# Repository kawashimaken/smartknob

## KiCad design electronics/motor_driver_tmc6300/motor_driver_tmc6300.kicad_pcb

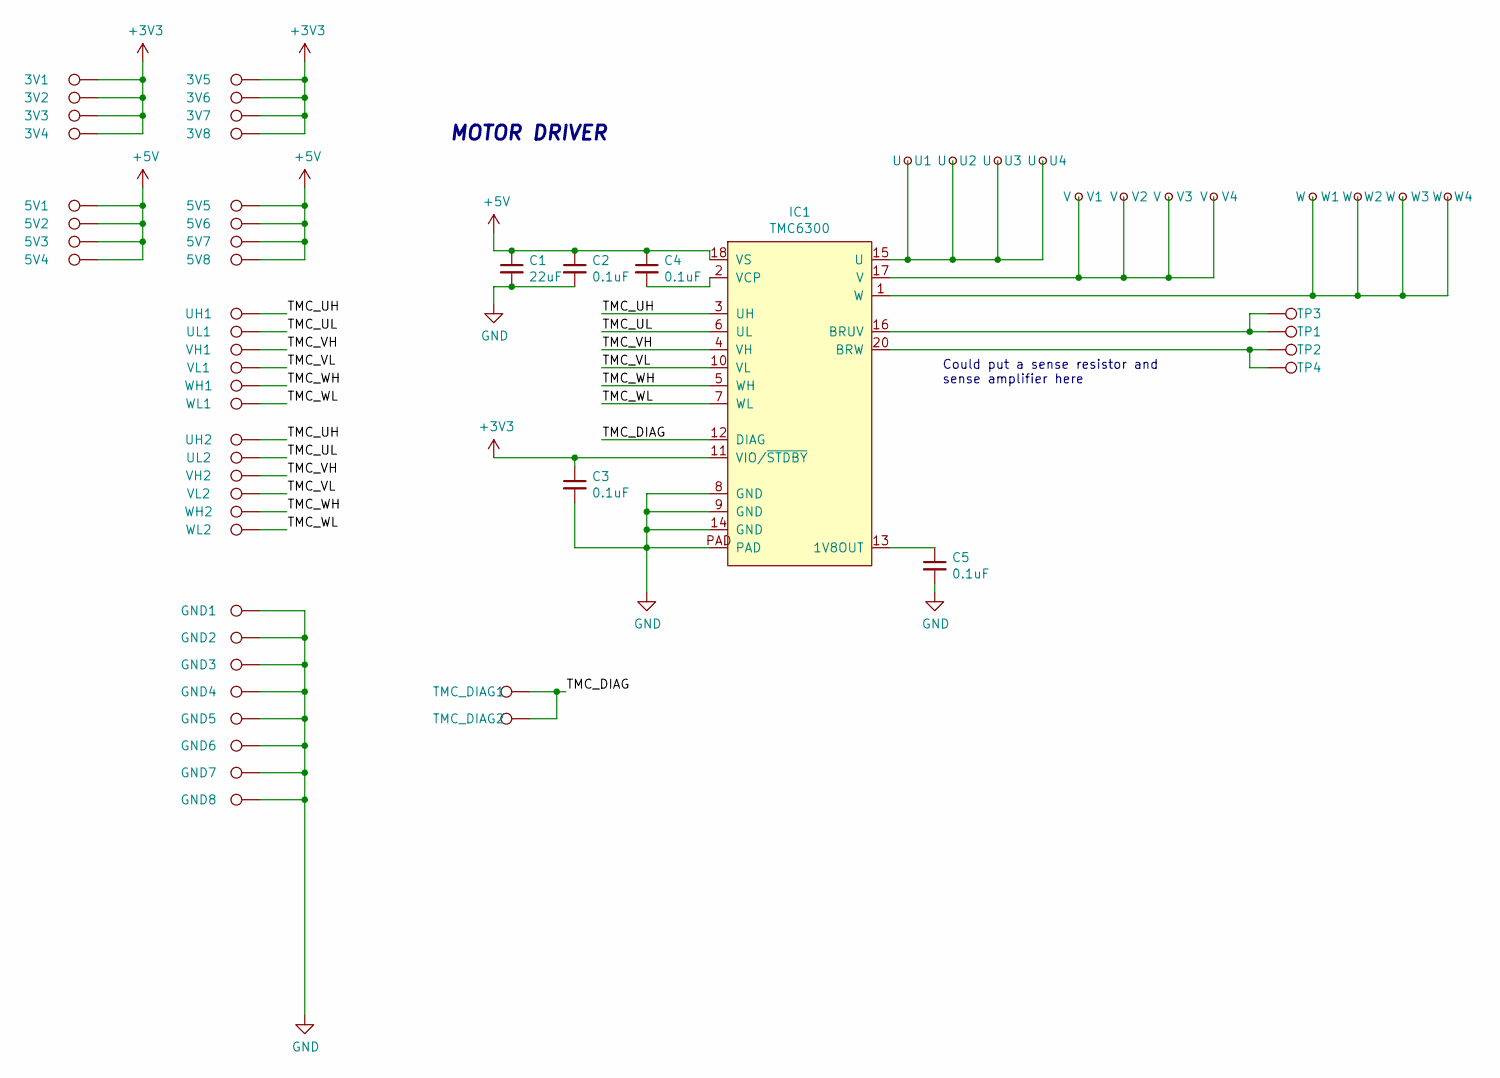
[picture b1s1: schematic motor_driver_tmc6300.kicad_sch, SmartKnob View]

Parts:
3V1, 3V2, 3V3, 3V4, 3V5, 3V6, 3V7, 3V8, 5V1, 5V2, 5V3, 5V4, 5V5, 5V6, 5V7, 5V8: TestPoint; kawashima_TestPoint_THTPad_D1.5mm_Drill0.7mm
C1: 22uF; C_0805_2012Metric_Pad1.18x1.45mm_HandSolder; LCSC C98190
C2, C3, C4, C5: 0.1uF; C_0603_1608Metric_Pad1.08x0.95mm_HandSolder; LCSC C1591
GND1, GND2, GND3, GND4, GND5, GND6, GND7, GND8: TestPoint; kawashima_TestPoint_THTPad_D1.5mm_Drill0.7mm
IC1: TMC6300; QFN-20-1EP_3x3mm_P0.4mm_EP1.65x1.65mm_ThermalVias_LargerVia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; Digikey TMC6300-LA-T
TMC_DIAG1, TMC_DIAG2: TestPoint; kawashima_TestPoint_THTPad_D1.5mm_Drill0.7mm
TP1, TP2, TP3, TP4: TestPoint; kawashima_TestPoint_THTPad_D1.5mm_Drill0.7mm
U1, U2, U3, U4: U; kawashima_TestPoint_THTPad_D1.5mm_Drill0.7mm
UH1, UH2: TestPoint; kawashima_TestPoint_THTPad_D1.5mm_Drill0.7mm
UL1, UL2: TestPoint; kawashima_TestPoint_THTPad_D1.5mm_Drill0.7mm
V1, V2, V3, V4: V; kawashima_TestPoint_THTPad_D1.5mm_Drill0.7mm
VH1, VH2: TestPoint; kawashima_TestPoint_THTPad_D1.5mm_Drill0.7mm
VL1, VL2: TestPoint; kawashima_TestPoint_THTPad_D1.5mm_Drill0.7mm
W1, W2, W3, W4: W; kawashima_TestPoint_THTPad_D1.5mm_Drill0.7mm
WH1, WH2: TestPoint; kawashima_TestPoint_THTPad_D1.5mm_Drill0.7mm
WL1, WL2: TestPoint; kawashima_TestPoint_THTPad_D1.5mm_Drill0.7mm

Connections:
+3V3: 3V1.1, 3V2.1, 3V3.1, 3V4.1, 3V5.1, 3V6.1, 3V7.1, 3V8.1, C3.1, IC1.11 (VIO/~STDBY)
+5V: 5V1.1, 5V2.1, 5V3.1, 5V4.1, 5V5.1, 5V6.1, 5V7.1, 5V8.1, C1.1, C2.1, C4.1, IC1.18 (VS)
/TMC_DIAG: IC1.12 (DIAG), TMC_DIAG1.1, TMC_DIAG2.1
/TMC_UH: IC1.3 (UH), UH1.1, UH2.1
/TMC_UL: IC1.6 (UL), UL1.1, UL2.1
/TMC_VH: IC1.4 (VH), VH1.1, VH2.1
/TMC_VL: IC1.10 (VL), VL1.1, VL2.1
/TMC_WH: IC1.5 (WH), WH1.1, WH2.1
/TMC_WL: IC1.7 (WL), WL1.1, WL2.1
GND: C1.2, C2.2, C3.2, C5.2, GND1.1, GND2.1, GND3.1, GND4.1, GND5.1, GND6.1, GND7.1, GND8.1, IC1.8 (GND), IC1.9 (GND), IC1.14 (GND), IC1.PAD
unnamed: C5.1, IC1.13 (1V8OUT)
unnamed: IC1.16 (BRUV), TP1.1, TP3.1
unnamed: IC1.20 (BRW), TP2.1, TP4.1
unnamed: IC1.15 (U), U1.1, U2.1, U3.1, U4.1
unnamed: IC1.17 (V), V1.1, V2.1, V3.1, V4.1
unnamed: C4.2, IC1.2 (VCP)
unnamed: IC1.1 (W), W1.1, W2.1, W3.1, W4.1

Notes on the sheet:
Could put a sense resistor and sense amplifier here
MOTOR DRIVER

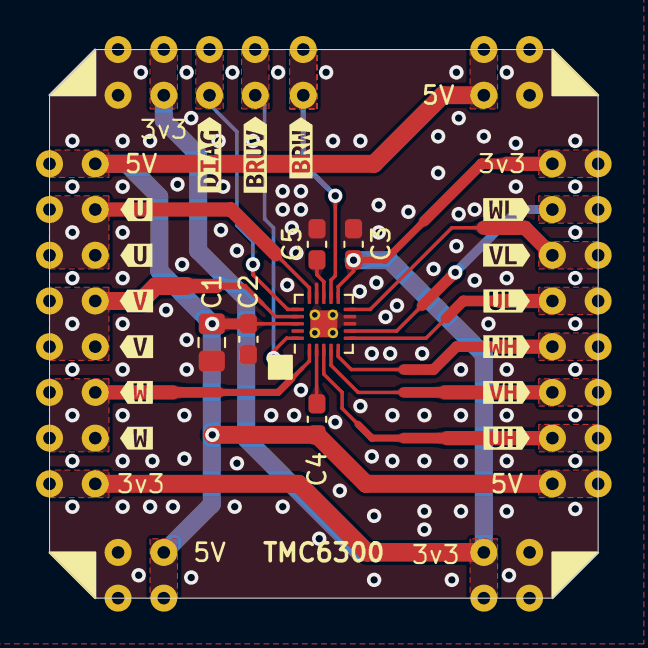
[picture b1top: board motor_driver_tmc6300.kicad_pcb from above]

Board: 2 copper layers, 30.5 x 30.5 mm, 75 parts (0 on the bottom side), 17 nets.

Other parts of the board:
kibuzzard-6701E86E, kibuzzard-6701E86E#2: G***; kibuzzard-6701E86E
kibuzzard-6701E87B, kibuzzard-6701E87B#2: G***; kibuzzard-6701E87B
kibuzzard-6701E882, kibuzzard-6701E882#2: G***; kibuzzard-6701E882
kibuzzard-670234D9: G***; kibuzzard-670234D9
kibuzzard-6702202C: G***; kibuzzard-6702202C
kibuzzard-6702204D: G***; kibuzzard-6702204D
kibuzzard-6702206A: G***; kibuzzard-6702206A
kibuzzard-67022038: G***; kibuzzard-67022038
kibuzzard-67022043: G***; kibuzzard-67022043
kibuzzard-67022085: G***; kibuzzard-67022085
kibuzzard-67032619: G***; kibuzzard-67032619
kibuzzard-67032626: G***; kibuzzard-67032626

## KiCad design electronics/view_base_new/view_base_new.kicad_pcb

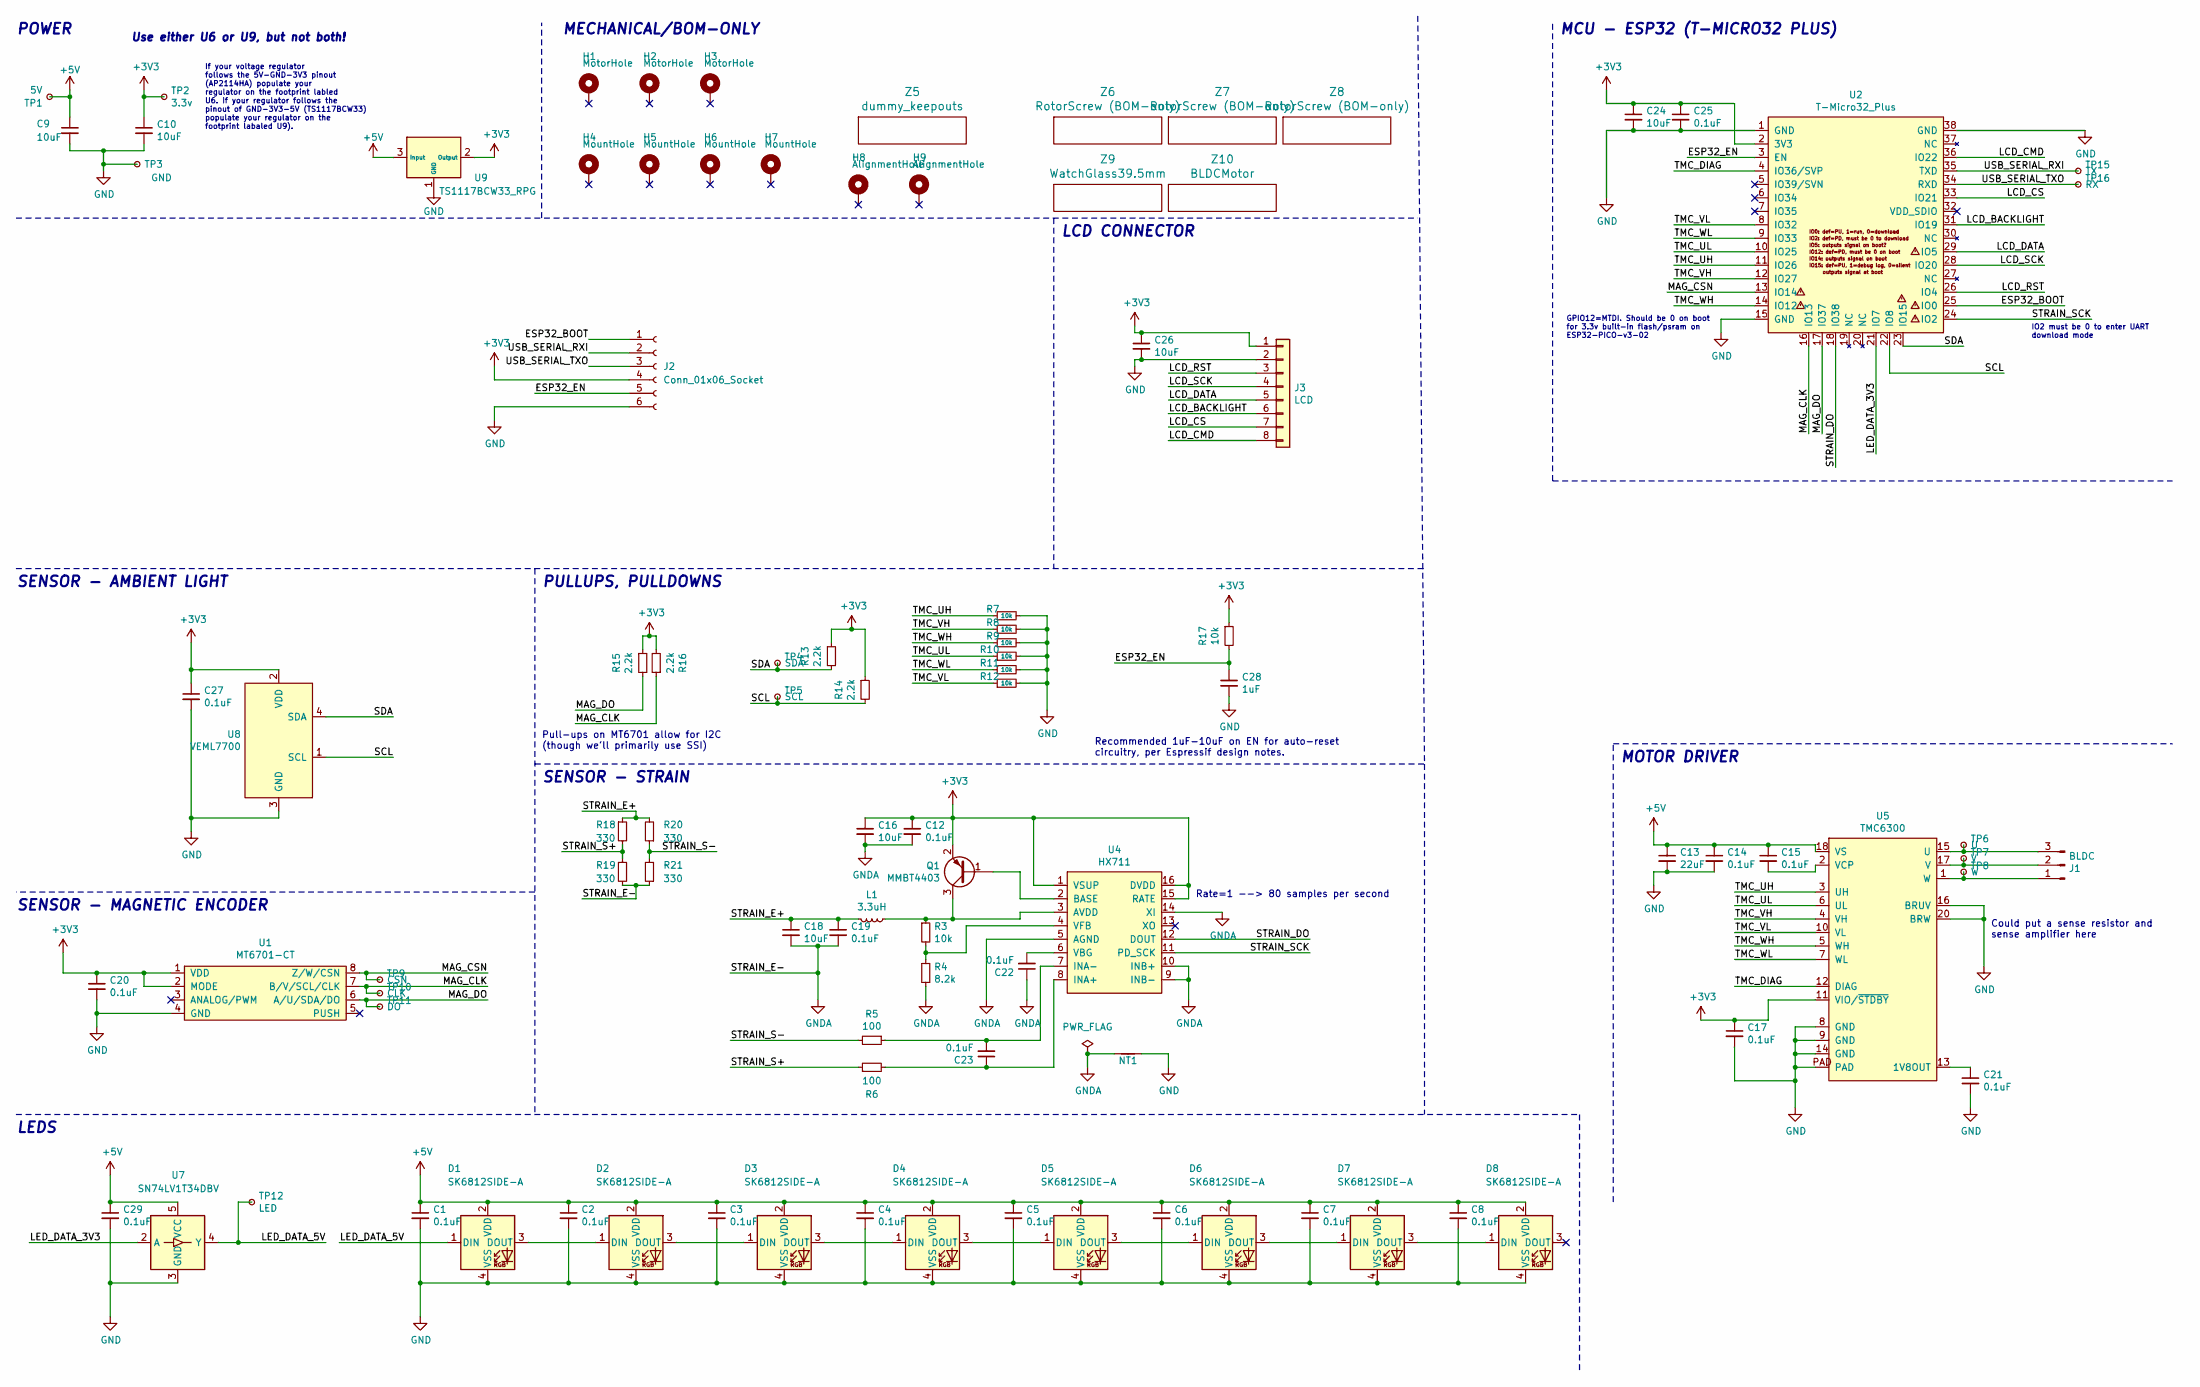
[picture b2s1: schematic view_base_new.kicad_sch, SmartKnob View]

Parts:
C1, C2, C3, C4, C5, C6, C7, C8, C12, C14, C15, C17, C19, C20, C21, C22, C23: 0.1uF; C_0603_1608Metric; LCSC C1591
C9, C10, C16, C18, C24: 10uF; C_0805_2012Metric; LCSC C15850
C13: 22uF; C_0805_2012Metric; LCSC C98190
C25, C27, C29: 0.1uF; C_0603_1608Metric_Pad1.08x0.95mm_HandSolder; LCSC C1591
C26: 10uF; C_0805_2012Metric_Pad1.18x1.45mm_HandSolder; LCSC C15850
C28: 1uF; C_0603_1608Metric_Pad1.08x0.95mm_HandSolder; Mouser 187-CL10A105KA8NNNC
D1, D2, D3, D4, D5, D6, D7, D8: SK6812SIDE-A; SK6812-SIDE-A; Digikey 1528-4691-ND
H1, H2, H3: MotorHole; MountingHole_M1.6; LCSC C2931389
H4, H5, H6, H7: MountHole; MountingHole_2.2mm_M2_ISO7380_Pad_NonVirtual; LCSC C2911210 or C2911532 (screw), C2961595 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
H8, H9: AlignmentHole; MountingHole_2.2mm_M2_ISO7380_Pad_NonVirtual
J1: BLDC; 532610371; LCSC C293630
J2: Conn_01x06_Socket; PinHeader_1x06_P2.54mm_Vertical
J3: LCD; SolderPads_2mm_8
L1: 3.3uH; L_0805_2012Metric; LCSC C307744
NT1: NetTie_2; NetTie-2_SMD_Pad0.5mm
Q1: MMBT4403; SOT-23; LCSC C78864
R3, R7, R8, R9, R10, R11, R12, R17: 10k; R_0603_1608Metric; LCSC C98220
R4: 8.2k; R_0603_1608Metric; LCSC C114637
R5, R6: 100; R_0603_1608Metric; LCSC C319953
R13, R14, R15, R16: 2.2k; R_0603_1608Metric; LCSC C4190
R18, R19, R20, R21: 330; R_2512_6332Metric; LCSC C19866
TP1: 5V; TestPoint_Pad_D2.0mm_ValueSilk
TP2: 3.3v; TestPoint_Pad_D2.0mm_ValueSilk
TP3: GND; TestPoint_Pad_D2.0mm_ValueSilk
TP4: SDA; TestPoint_Pad_D2.0mm_ValueSilk
TP5: SCL; TestPoint_Pad_D2.0mm_ValueSilk
TP6: U; TestPoint_Pad_D2.0mm_ValueSilk
TP7: V; TestPoint_Pad_D2.0mm_ValueSilk
TP8: W; TestPoint_Pad_D2.0mm_ValueSilk
TP9: CSN; TestPoint_Pad_D2.0mm_ValueSilk
TP10: CLK; TestPoint_Pad_D2.0mm_ValueSilk
TP11: DO; TestPoint_Pad_D2.0mm_ValueSilk
TP12: LED; TestPoint_Pad_D2.0mm_ValueSilk
TP15: TX; TestPoint_Pad_D2.0mm_ValueSilk
TP16: RX; TestPoint_Pad_D2.0mm_ValueSilk
U1: MT6701-CT; SOIC-8_3.9x4.9mm_P1.27mm; LCSC C2856764, or C3003196
U2: T-Micro32_Plus; T-Micro32; Digikey N/A
U4: HX711; SOIC-16_3.9x9.9mm_P1.27mm; LCSC C43656
U5: TMC6300; QFN-20-1EP_3x3mm_P0.4mm_EP1.65x1.65mm_ThermalVias_LargerVia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; Digikey TMC6300-LA-T
U7: SN74LV1T34DBV; SOT-23-5; LCSC C100024
U8: VEML7700; VEML7700-TOP; Digikey VEML7700-TT
U9: TS1117BCW33_RPG; SOT-223-3_TabPin2_GndOutIn; LCSC C6186, C35879, or others
Z5: dummy_keepouts; ViewKeepouts3d
Z6, Z7, Z8: RotorScrew (BOM-only); bom_only_no_pin
Z9: WatchGlass39.5mm; bom_only_no_pin
Z10: BLDCMotor; bom_only_no_pin

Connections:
+3V3: C10.1, C12.1, C16.1, C17.1, C20.1, C24.1, C25.1, C26.1, C27.1, J2.4, J3.1, Q1.2 (E), R13.1, R14.1, R15.1, R16.2, R17.1, TP2.1, U1.1 (VDD), U1.2 (MODE), U2.2 (3V3), U4.1 (VSUP), U4.15 (RATE), U4.16 (DVDD), U5.11 (VIO/~STDBY), U8.2 (VDD), U9.2 (Output)
+5V: C1.1, C2.1, C3.1, C4.1, C5.1, C6.1, C7.1, C8.1, C9.1, C13.1, C14.1, C15.1, C29.1, D1.2 (VDD), D2.2 (VDD), D3.2 (VDD), D4.2 (VDD), D5.2 (VDD), D6.2 (VDD), D7.2 (VDD), D8.2 (VDD), TP1.1, U5.18 (VS), U7.5 (VCC), U9.3 (Input)
/ESP32_BOOT: J2.1, U2.25 (IO0)
/ESP32_EN: C28.1, J2.5, R17.2, U2.3 (EN)
/LCD_BACKLIGHT: J3.6, U2.31 (IO19)
/LCD_CMD: J3.8, U2.36 (IO22)
/LCD_CS: J3.7, U2.33 (IO21)
/LCD_DATA: J3.5, U2.29 (IO5)
/LCD_RST: J3.3, U2.26 (IO4)
/LCD_SCK: J3.4, U2.28 (IO20)
/LED_DATA_3V3: U2.21 (IO7), U7.2 (A)
/LED_DATA_5V: D1.1 (DIN), TP12.1, U7.4 (Y)
/MAG_CLK: R16.1, TP10.1, U1.7 (B/V/SCL/CLK), U2.16 (IO13)
/MAG_CSN: TP9.1, U1.8 (Z/W/CSN), U2.13 (IO14)
/MAG_DO: R15.2, TP11.1, U1.6 (A/U/SDA/DO), U2.17 (IO37)
/SCL: R14.2, TP5.1, U2.22 (IO8), U8.1 (SCL)
/SDA: R13.2, TP4.1, U2.23 (IO15), U8.4 (SDA)
/STRAIN_DO: U2.18 (IO38), U4.12 (DOUT)
/STRAIN_E+: C18.1, C19.1, L1.2, R18.1, R20.2
/STRAIN_S+: R6.1, R18.2, R19.1
/STRAIN_S-: R5.2, R20.1, R21.2
/STRAIN_SCK: U2.24 (IO2), U4.11 (PD_SCK)
/TMC_DIAG: U2.4 (IO36/SVP), U5.12 (DIAG)
/TMC_UH: R7.1, U2.11 (IO26), U5.3 (UH)
/TMC_UL: R10.1, U2.10 (IO25), U5.6 (UL)
/TMC_VH: R8.1, U2.12 (IO27), U5.4 (VH)
/TMC_VL: R12.1, U2.8 (IO32), U5.10 (VL)
/TMC_WH: R9.1, U2.14 (IO12), U5.5 (WH)
/TMC_WL: R11.1, U2.9 (IO33), U5.7 (WL)
/USB_SERIAL_RXI: J2.2, TP15.1, U2.35 (TXD)
/USB_SERIAL_TXO: J2.3, TP16.1, U2.34 (RXD)
GND: C1.2, C2.2, C3.2, C4.2, C5.2, C6.2, C7.2, C8.2, C9.2, C10.2, C13.2, C14.2, C17.2, C20.2, C21.2, C24.2, C25.2, C26.2, C27.2, C28.2, C29.2, D1.4 (VSS), D2.4 (VSS), D3.4 (VSS), D4.4 (VSS), D5.4 (VSS), D6.4 (VSS), D7.4 (VSS), D8.4 (VSS), J2.6, J3.2, NT1.2, R7.2, R8.2, R9.2, R10.2, R11.2, R12.2, TP3.1, U1.4 (GND), U2.1 (GND), U2.15 (GND), U2.38 (GND), U5.8 (GND), U5.9 (GND), U5.14 (GND), U5.16 (BRUV), U5.20 (BRW), U5.PAD, U7.3 (GND), U8.3 (GND), U9.1 (GND)
GNDA: C12.2, C16.2, C18.2, C19.2, C22.1, NT1.1, R4.2, R19.2, R21.1, U4.5 (AGND), U4.9 (INB-), U4.10 (INB+), U4.14 (XI)
unnamed: D1.3 (DOUT), D2.1 (DIN)
unnamed: D2.3 (DOUT), D3.1 (DIN)
unnamed: D3.3 (DOUT), D4.1 (DIN)
unnamed: D4.3 (DOUT), D5.1 (DIN)
unnamed: D5.3 (DOUT), D6.1 (DIN)
unnamed: D6.3 (DOUT), D7.1 (DIN)
unnamed: D7.3 (DOUT), D8.1 (DIN)
unnamed: J1.1, TP8.1, U5.1 (W)
unnamed: J1.2, TP7.1, U5.17 (V)
unnamed: J1.3, TP6.1, U5.15 (U)
unnamed: Q1.1 (B), U4.2 (BASE)
unnamed: L1.1, Q1.3 (C), R3.1, U4.3 (AVDD)
unnamed: C23.1, R6.2, U4.8 (INA+)
unnamed: C23.2, R5.1, U4.7 (INA-)
unnamed: C22.2, U4.6 (VBG)
unnamed: R3.2, R4.1, U4.4 (VFB)
unnamed: C21.1, U5.13 (1V8OUT)
unnamed: C15.2, U5.2 (VCP)

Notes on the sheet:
POWER
Could put a sense resistor and sense amplifier here
MCU - ESP32 (T-MICRO32 PLUS)
If your voltage regulator follows the 5V-GND-3V3 pinout (AP2114HA) populate your regulator on the footprint labled U6. If your regulator follows the pinout of GND-3V3-5V (TS1117BCW33) populate your regulator on the footprint labaled U9).
SENSOR - MAGNETIC ENCODER
MOTOR DRIVER
MECHANICAL/BOM-ONLY
IO2 must be 0 to enter UART download mode
GPIO12=MTDI. Should be 0 on boot for 3.3v built-in flash/psram on ESP32-PICO-v3-02
Pull-ups on MT6701 allow for I2C (though we'll primarily use SSI)
Use either U6 or U9, but not both!
Rate=1 --> 80 samples per second
SENSOR - AMBIENT LIGHT
Recommended 1uF-10uF on EN for auto-reset circuitry, per Espressif design notes.
SENSOR - STRAIN
LEDS
PULLUPS, PULLDOWNS
LCD CONNECTOR

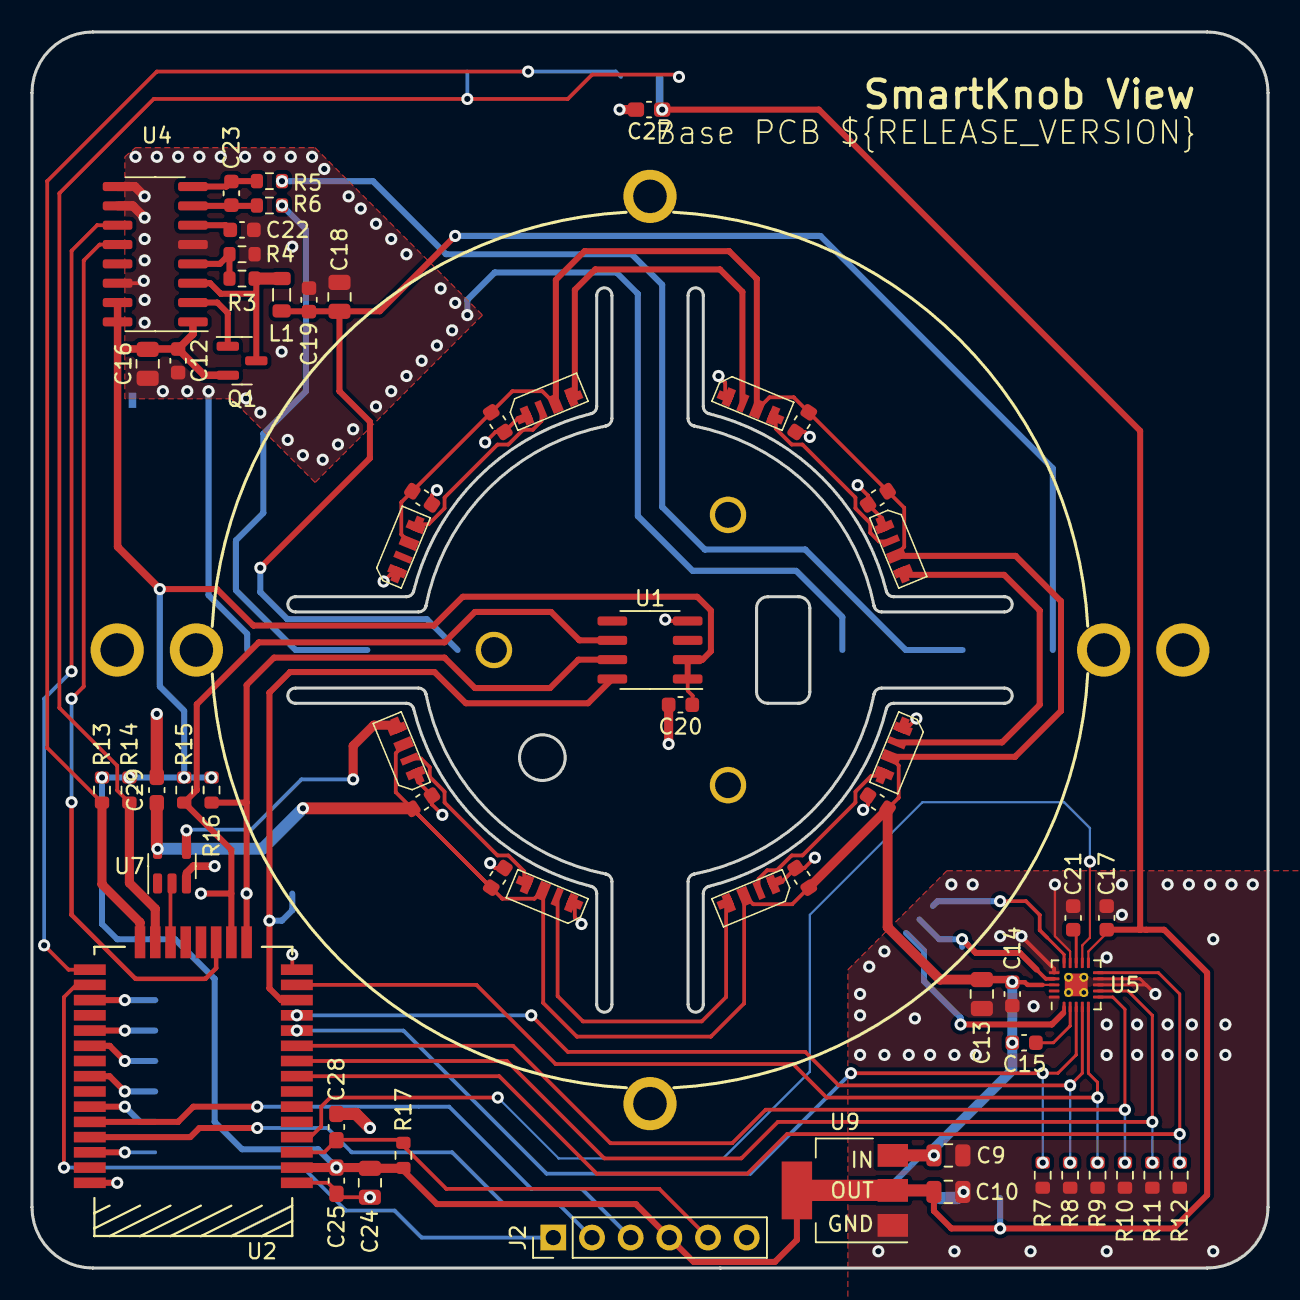
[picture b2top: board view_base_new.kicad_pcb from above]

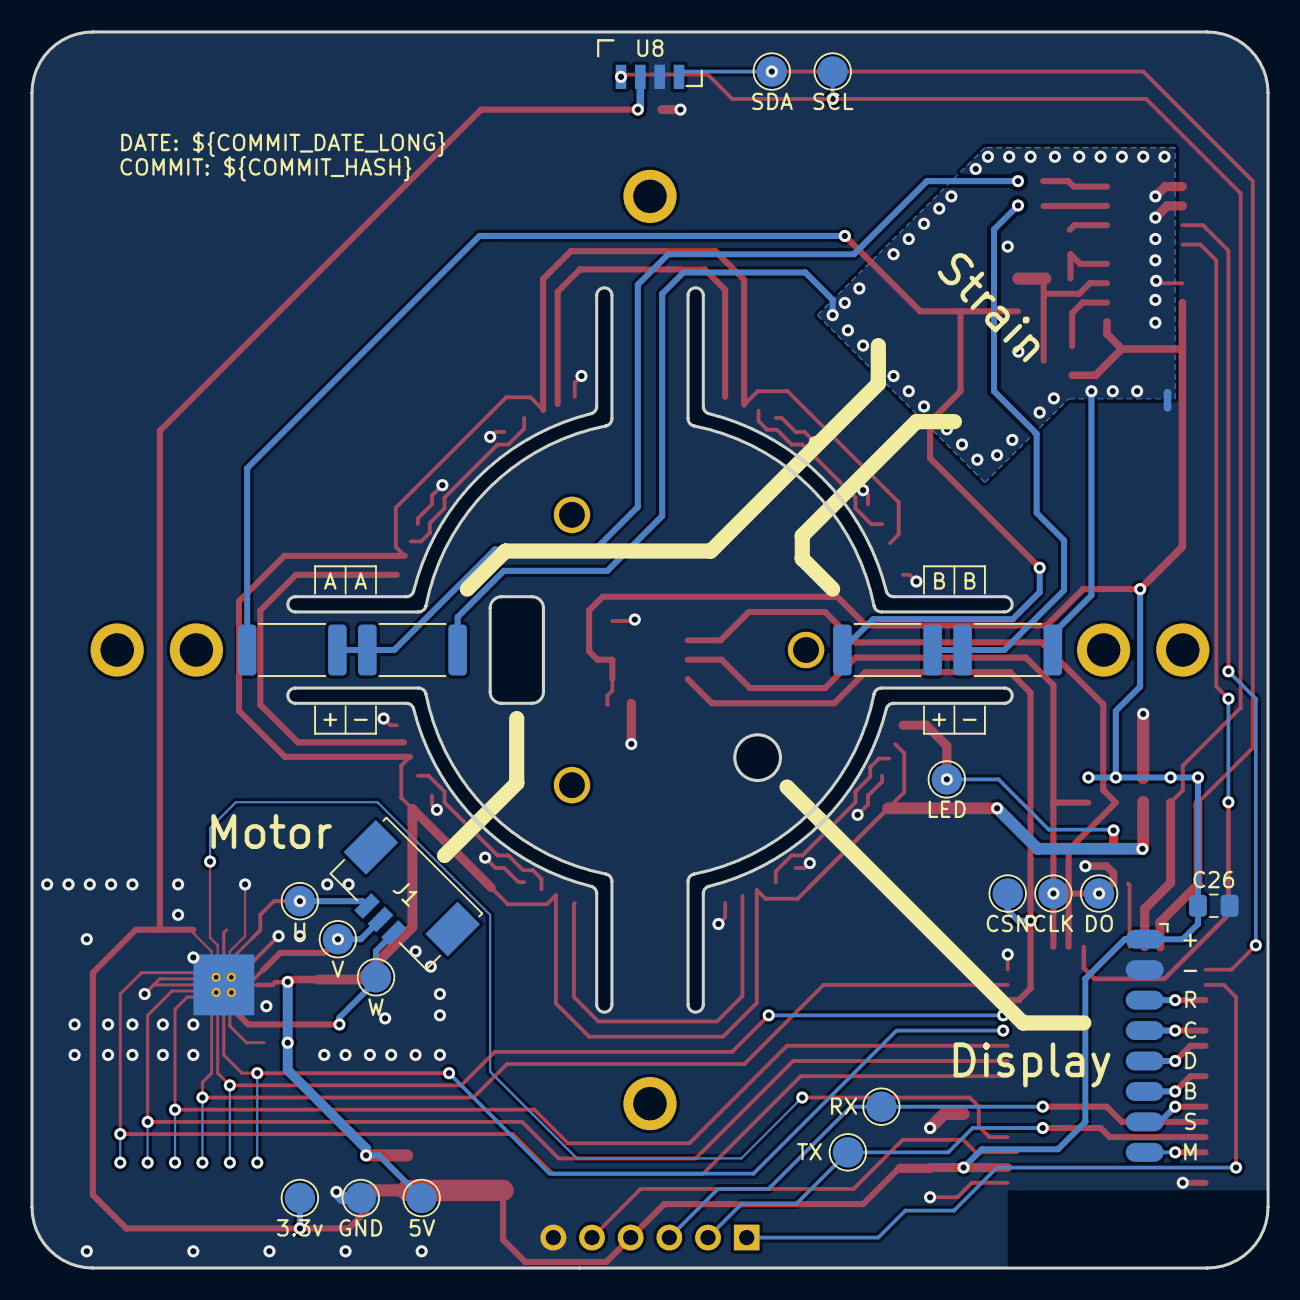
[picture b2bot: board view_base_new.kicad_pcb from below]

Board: 2 copper layers, 81.2 x 81.2 mm, 97 parts (23 on the bottom side), 51 nets.

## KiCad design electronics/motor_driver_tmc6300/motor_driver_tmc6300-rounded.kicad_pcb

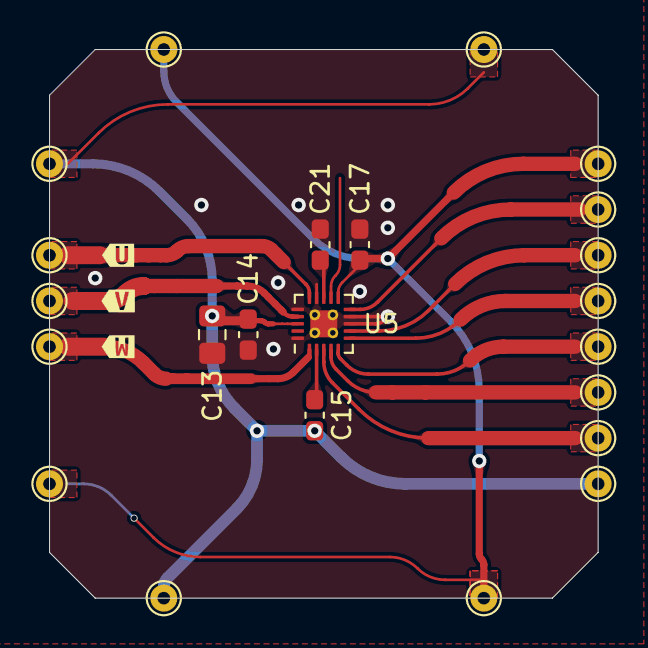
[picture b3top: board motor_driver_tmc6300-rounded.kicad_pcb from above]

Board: 2 copper layers, 30.5 x 30.5 mm, 26 parts (0 on the bottom side), 14 nets.

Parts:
3V1, 3V2, 3V3, 3V4, 5V1, 5V2, 5V3, 5V4: TestPoint; TestPoint_THTPad_D1.5mm_Drill0.7mm
C13: 22uF; C_0805_2012Metric_Pad1.18x1.45mm_HandSolder
C14, C15, C17, C21: 0.1uF; C_0603_1608Metric_Pad1.08x0.95mm_HandSolder
U1: U; TestPoint_THTPad_D1.5mm_Drill0.7mm
U5: TMC6300; QFN-20-1EP_3x3mm_P0.4mm_EP1.65x1.65mm_ThermalVias_LargerVia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
UH1: TestPoint; TestPoint_THTPad_D1.5mm_Drill0.7mm
UL1: TestPoint; TestPoint_THTPad_D1.5mm_Drill0.7mm
V1: V; TestPoint_THTPad_D1.5mm_Drill0.7mm
VH1: TestPoint; TestPoint_THTPad_D1.5mm_Drill0.7mm
VL1: TestPoint; TestPoint_THTPad_D1.5mm_Drill0.7mm
W1: W; TestPoint_THTPad_D1.5mm_Drill0.7mm
WH1: TestPoint; TestPoint_THTPad_D1.5mm_Drill0.7mm
WL1: TestPoint; TestPoint_THTPad_D1.5mm_Drill0.7mm
kibuzzard-6701E86E: G***; kibuzzard-6701E86E
kibuzzard-6701E87B: G***; kibuzzard-6701E87B
kibuzzard-6701E882: G***; kibuzzard-6701E882

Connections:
+3V3: 3V1.1, 3V2.1, 3V3.1, 3V4.1, C17.1, U5.11 (VIO/~STDBY)
+5V: 5V1.1, 5V2.1, 5V3.1, 5V4.1, C13.1, C14.1, C15.1, U5.18 (VS)
/TMC_UH: U5.3 (UH), UH1.1
/TMC_UL: U5.6 (UL), UL1.1
/TMC_VH: U5.4 (VH), VH1.1
/TMC_VL: U5.10 (VL), VL1.1
/TMC_WH: U5.5 (WH), WH1.1
/TMC_WL: U5.7 (WL), WL1.1
GND: C13.2, C14.2, C17.2, C21.2, U5.8 (GND), U5.9 (GND), U5.14 (GND), U5.16 (BRUV), U5.20 (BRW), U5.PAD
unnamed: C21.1, U5.13 (1V8OUT)
unnamed: U1.1, U5.15 (U)
unnamed: U5.17 (V), V1.1
unnamed: C15.2, U5.2 (VCP)
unnamed: U5.1 (W), W1.1

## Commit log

2024-06-30 add view_base_new
2024-06-30 improve routing
2024-07-02 tuning routing, save work
2024-07-02 change to hand soldering pad
2024-10-06 add tmc6300 motor driver board

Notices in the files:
parts and their libraries:
Copyright 2021 Accelerated Designs. All rights reserved.
